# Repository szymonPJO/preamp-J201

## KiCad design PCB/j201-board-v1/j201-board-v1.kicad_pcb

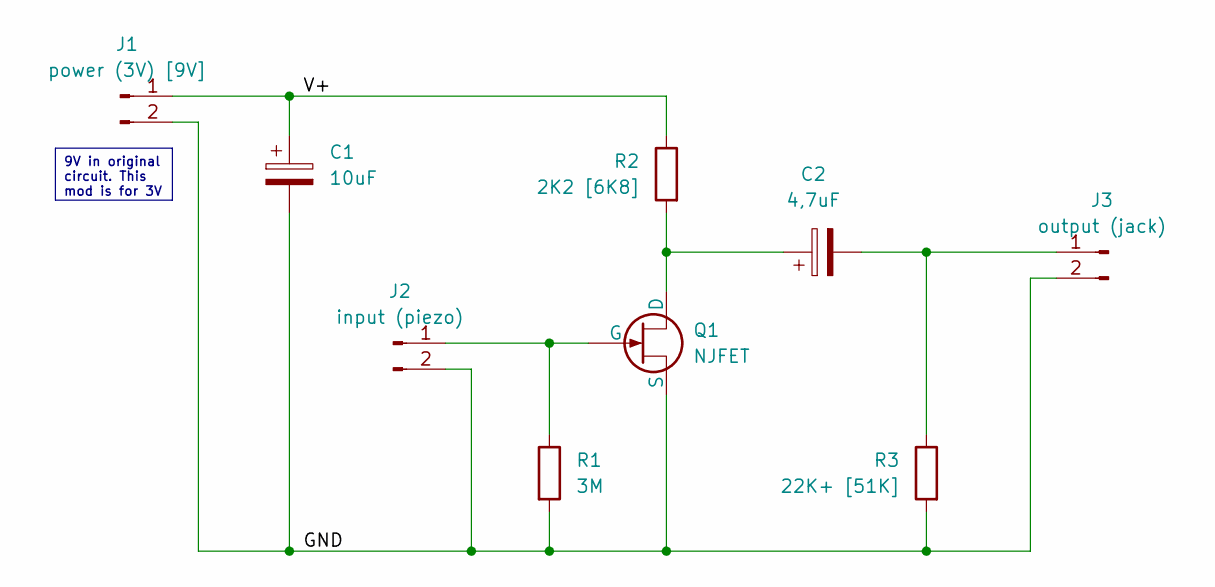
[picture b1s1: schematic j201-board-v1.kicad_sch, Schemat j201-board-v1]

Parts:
C1: 10uF; C_0805_2012Metric
C2: 4,7uF; C_0805_2012Metric
J1: power (3V) [9V]; P2
J2: input (piezo); P2
J3: output (jack); P2
Q1: NJFET; SOT-23
R1: 3M; R_0805_2012Metric
R2: 2K2 [6K8]; R_0805_2012Metric
R3: 22K+ [51K]; R_0805_2012Metric

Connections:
/GND: C1.2, J1.2, J2.2, J3.2, Q1.1 (S), R1.2, R3.2
/V+: C1.1, J1.1, R2.1
unnamed: J2.1, Q1.3 (G), R1.1
unnamed: C2.2, J3.1, R3.1
unnamed: C2.1, Q1.2 (D), R2.2

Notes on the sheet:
9V in original circuit. This mod is for 3V

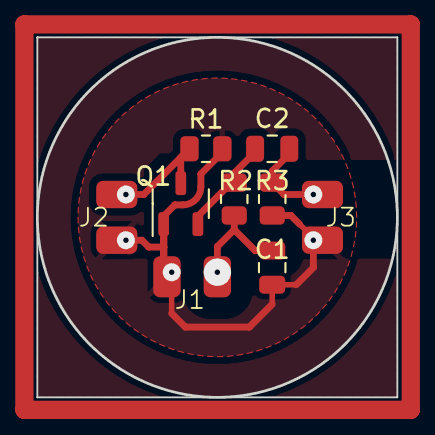
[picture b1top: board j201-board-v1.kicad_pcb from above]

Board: 2 copper layers, 20.0 x 20.0 mm, 9 parts (0 on the bottom side), 5 nets.

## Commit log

2023-08-03 img of schemats comparation
2023-08-03 base schematic
2023-08-08 update footprints
2023-08-09 board v1
2023-08-15 board design
2023-08-15 fix lib path
2023-08-15 pdf output
2023-08-15 remove useless folder
